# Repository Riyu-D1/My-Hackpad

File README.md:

## The HACKPAD

This is a simple yet functional macropad for devs and product designers therefore it includes 9 switches, a rotary encoder, and an oled display all powered by the seeduino xiao. 

## CAD

The case fits together using 4 M3 bolt and heat set inserts and the pcb is suspended via a sandwich style mount. I prints in 2 pieces to maintain minimalistic designed which is also followed by the vornoi design style. 

## Firmware

My Hack pad uses QMK firmware which i initialised and compiled in terminal 

## BOM

- 1 unsoldered Seeed XIAO RP2040
- 9x through-hole 1N4148 Diodes
- 9x MX-Style switches
- 1x EC11 Rotary encoders
- 1x 0.91 inch OLED display
- 9 white blank DSA keycaps
- 4x M3x16mm screws
- 4x 6x M3x5mx4mm heatset inserts

## Extra

This was my first attempt at pcb design and overall making a macropad so i am pretty happy with the results!

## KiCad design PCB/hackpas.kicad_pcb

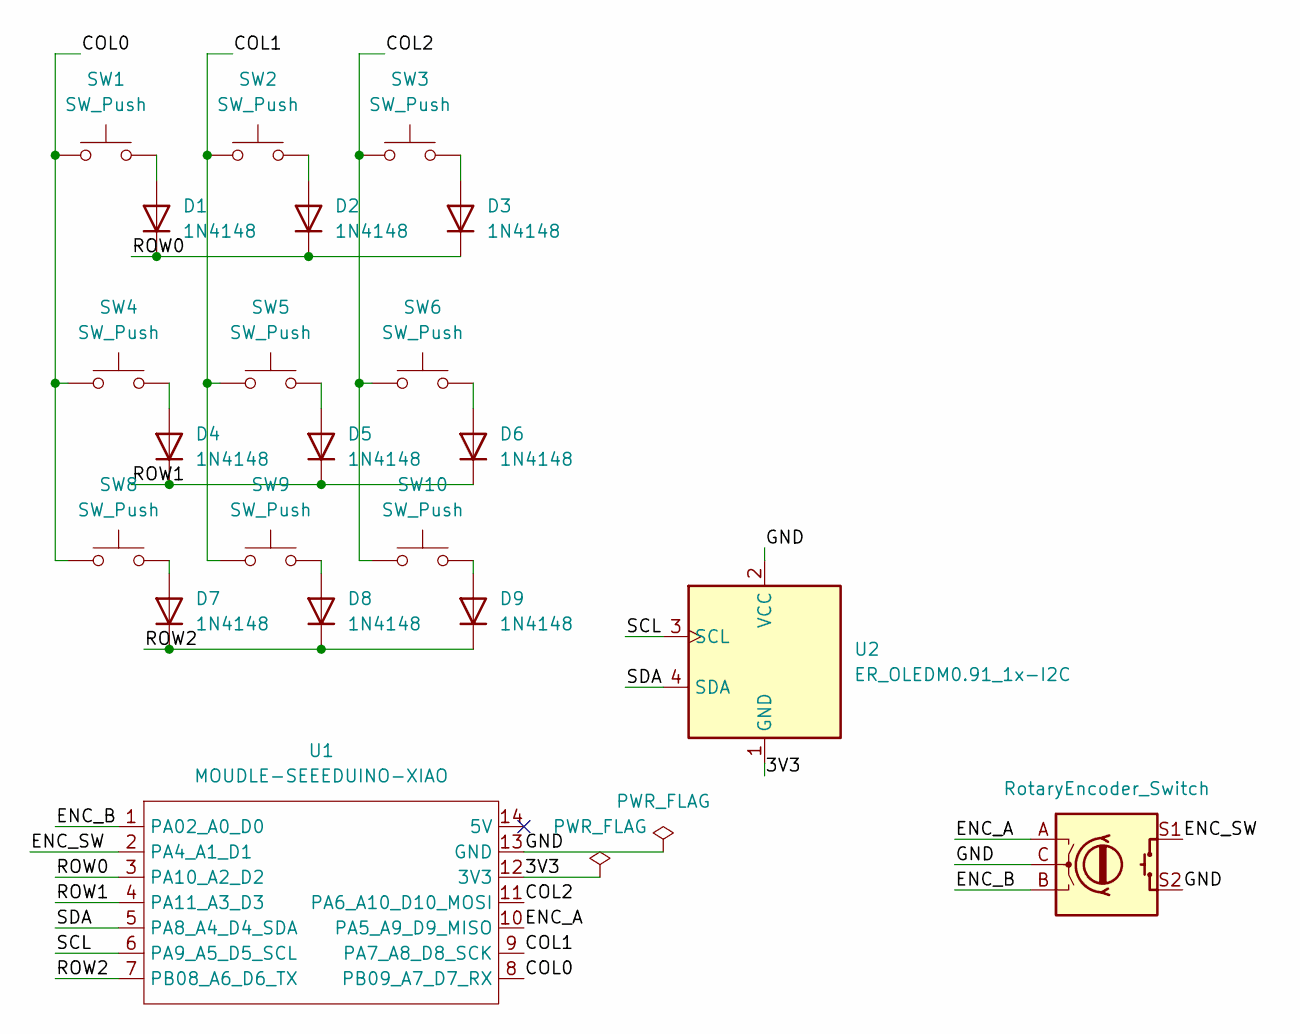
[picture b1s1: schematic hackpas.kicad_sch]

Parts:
D1, D2, D3, D4, D5, D6, D7, D8, D9: 1N4148; D_DO-35_SOD27_P7.62mm_Horizontal
SW1, SW2, SW3, SW4, SW5, SW6, SW8, SW9, SW10: SW_Push; SW_Cherry_MX_1.00u_PCB
SW7: RotaryEncoder_Switch; RotaryEncoder_Alps_EC11E-Switch_Vertical_H20mm
U1: MOUDLE-SEEEDUINO-XIAO; XIAO-Generic-Hybrid-14P-2.54-21X17.8MM
U2: ER_OLEDM0.91_1x-I2C

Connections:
/3V3: U1.12 (3V3), U2.1 (GND)
/COL0: SW1.1, SW4.1, SW8.1, U1.8 (PB09_A7_D7_RX)
/COL1: SW2.1, SW5.1, SW9.1, U1.9 (PA7_A8_D8_SCK)
/COL2: SW3.1, SW6.1, SW10.1, U1.11 (PA6_A10_D10_MOSI)
/ENC_A: SW7.A, U1.10 (PA5_A9_D9_MISO)
/ENC_B: SW7.B, U1.1 (PA02_A0_D0)
/ENC_SW: SW7.S1, U1.2 (PA4_A1_D1)
/GND: SW7.C, SW7.S2, U1.13 (GND), U2.2 (VCC)
/ROW0: D1.1 (K), D2.1 (K), D3.1 (K), U1.3 (PA10_A2_D2)
/ROW1: D4.1 (K), D5.1 (K), D6.1 (K), U1.4 (PA11_A3_D3)
/ROW2: D7.1 (K), D8.1 (K), D9.1 (K), U1.7 (PB08_A6_D6_TX)
/SCL: U1.6 (PA9_A5_D5_SCL), U2.3 (SCL)
/SDA: U1.5 (PA8_A4_D4_SDA), U2.4 (SDA)
unnamed: D1.2 (A), SW1.2
unnamed: D2.2 (A), SW2.2
unnamed: D3.2 (A), SW3.2
unnamed: D4.2 (A), SW4.2
unnamed: D5.2 (A), SW5.2
unnamed: D6.2 (A), SW6.2
unnamed: D7.2 (A), SW8.2
unnamed: D8.2 (A), SW9.2
unnamed: D9.2 (A), SW10.2

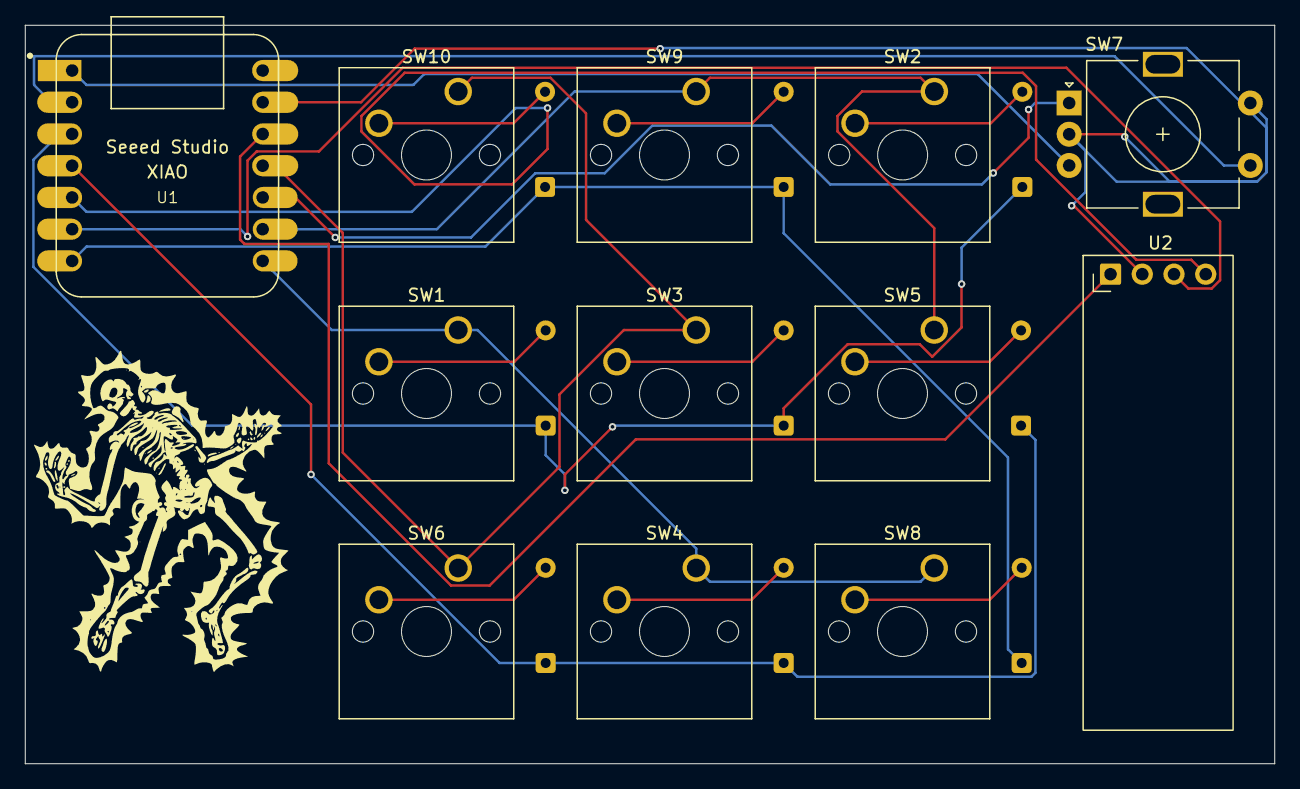
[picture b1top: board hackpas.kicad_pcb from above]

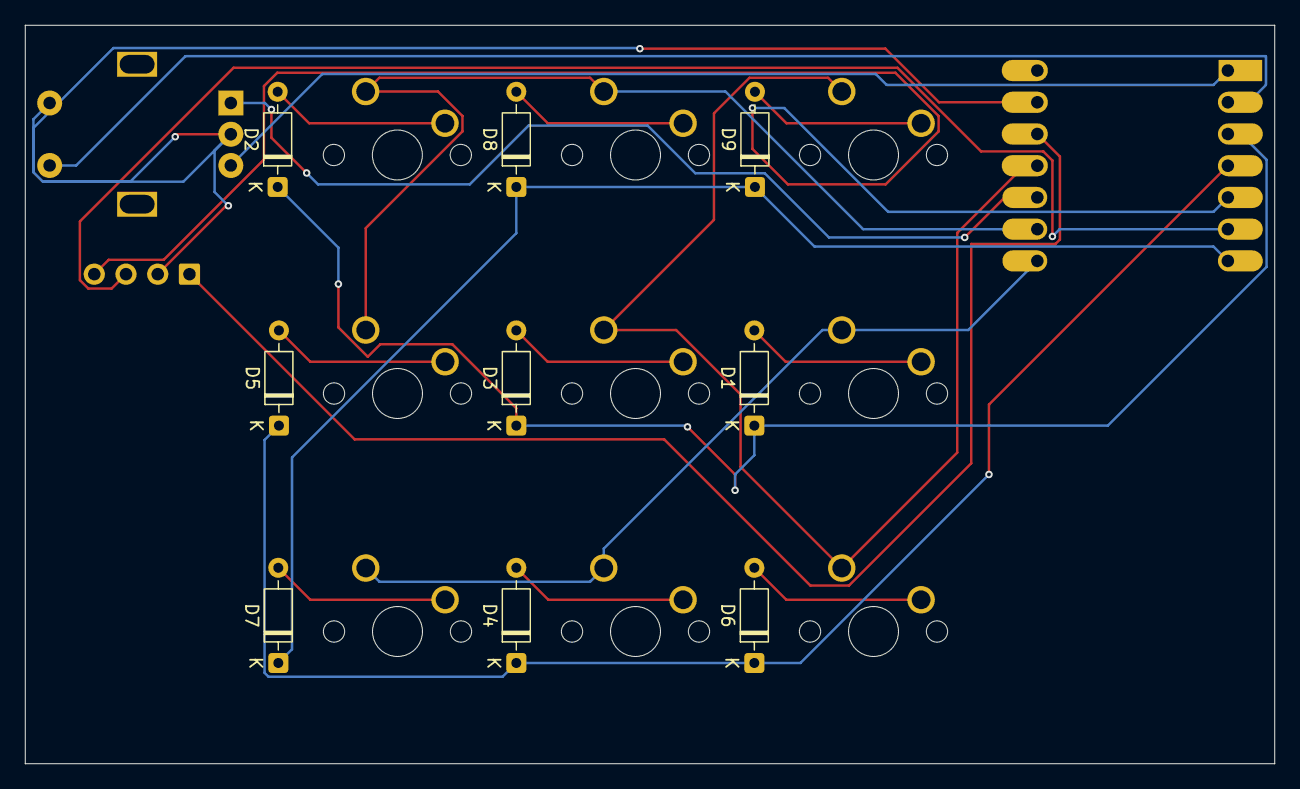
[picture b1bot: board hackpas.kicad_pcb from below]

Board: 2 copper layers, 100.0 x 59.1 mm, 21 parts (9 on the bottom side), 22 nets.
